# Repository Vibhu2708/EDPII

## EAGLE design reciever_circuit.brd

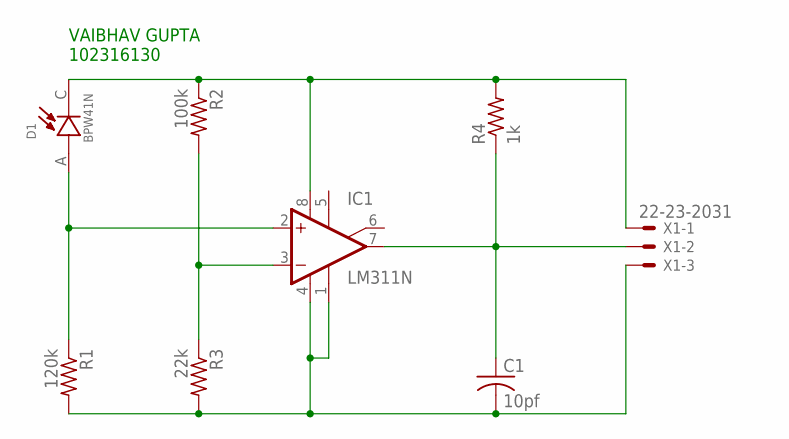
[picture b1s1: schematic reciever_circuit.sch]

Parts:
C1: 10pf; C025-024X044
D1: BPW41N; DIO_BPW41N
IC1: LM311N; DIL08
R1: 120k; 0204/5
R2: 100k; 0204/5
R3: 22k; 0204/5
R4: 1k; 0204/5
X1: 22-23-2031

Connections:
unnamed: D1.A, IC1.2 (+IN), R1.1
unnamed: IC1.3 (-IN), R2.2, R3.1
unnamed: D1.C, IC1.8 (V+), R2.1, R4.2, X1.1
unnamed: C1.1, IC1.7 (OUT), R4.1, X1.2
unnamed: C1.2, IC1.1 (GND), IC1.4 (V-), R1.2, R3.2, X1.3

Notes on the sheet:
VAIBHAV GUPTA 102316130

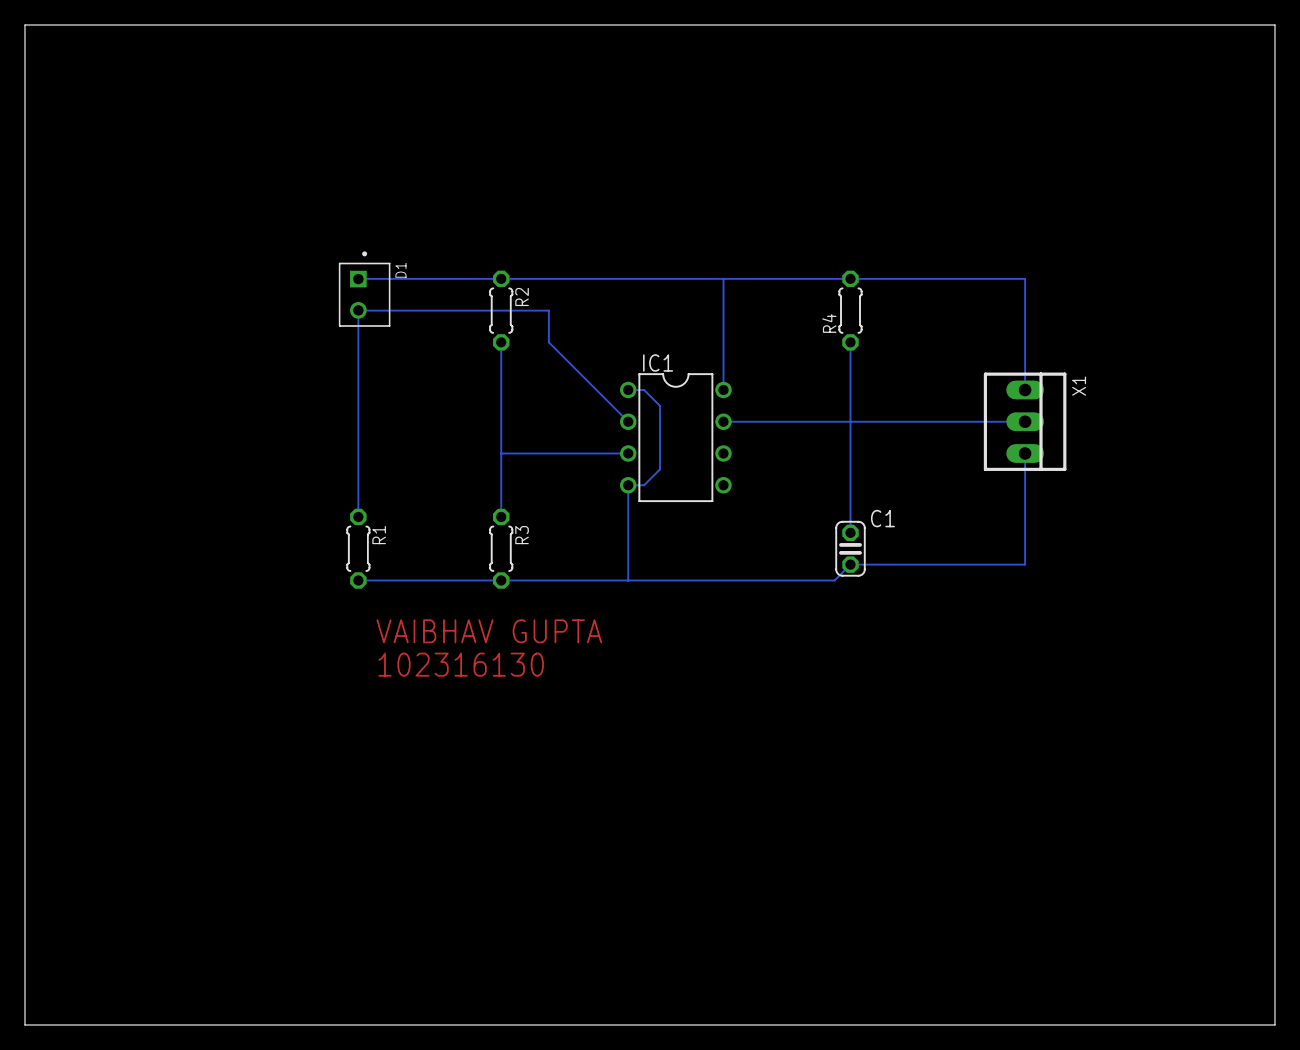
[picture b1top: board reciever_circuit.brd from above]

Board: 2 copper layers, 100.0 x 80.0 mm, 8 parts (0 on the bottom side), 5 nets.

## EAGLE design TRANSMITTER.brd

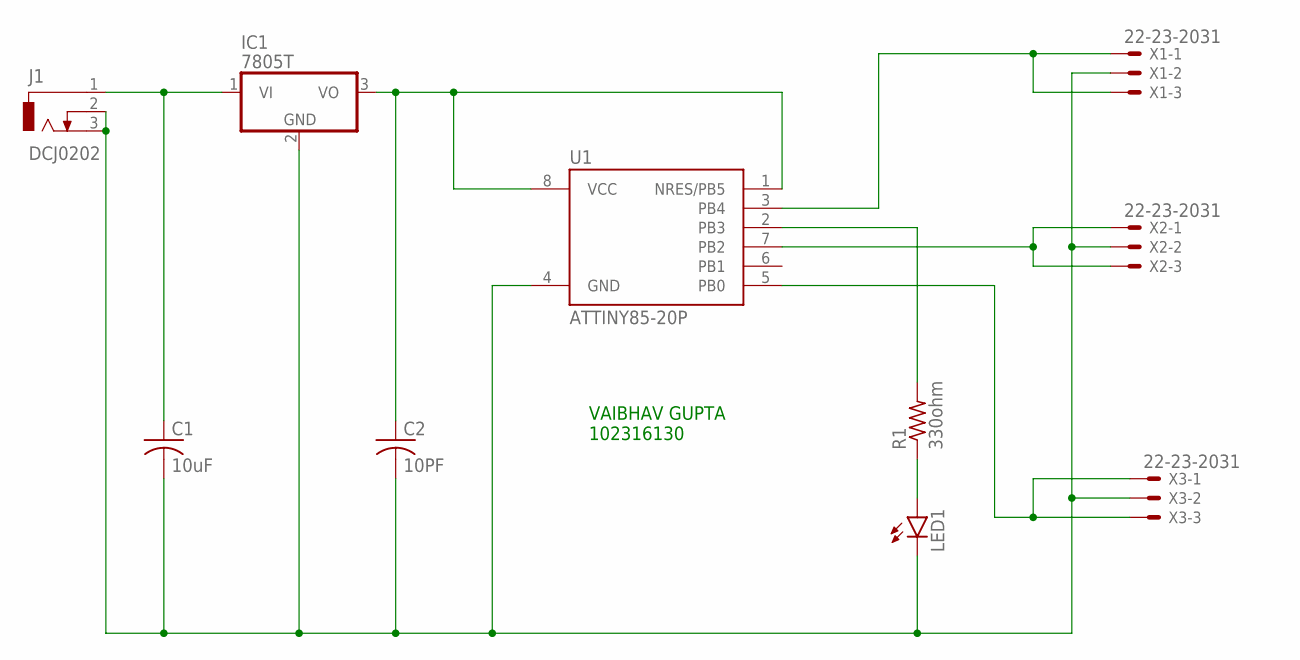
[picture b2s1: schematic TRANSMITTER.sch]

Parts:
C1: 10uF; C025-024X044
C2: 10PF; C025-024X044
IC1: 7805T; TO220H
J1: DCJ0202
LED1: LED3MM
R1: 330ohm; 0207/5V
U1: ATTINY85-20P; PDIP08_300MIL
X1, X2, X3: 22-23-2031

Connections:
unnamed: C1.1, IC1.1 (VI), J1.1
unnamed: C1.2, C2.2, IC1.2 (GND), J1.2, J1.3, LED1.K (C), U1.4 (GND), X1.2, X2.2, X3.2
unnamed: C2.1, IC1.3 (VO), U1.1 (NRES/PB5), U1.8 (VCC)
unnamed: U1.3 (PB4), X1.1, X1.3
unnamed: U1.5 (PB0), X3.1, X3.3
unnamed: R1.2, U1.2 (PB3)
unnamed: LED1.A, R1.1
unnamed: U1.7 (PB2), X2.1, X2.3

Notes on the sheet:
VAIBHAV GUPTA 102316130

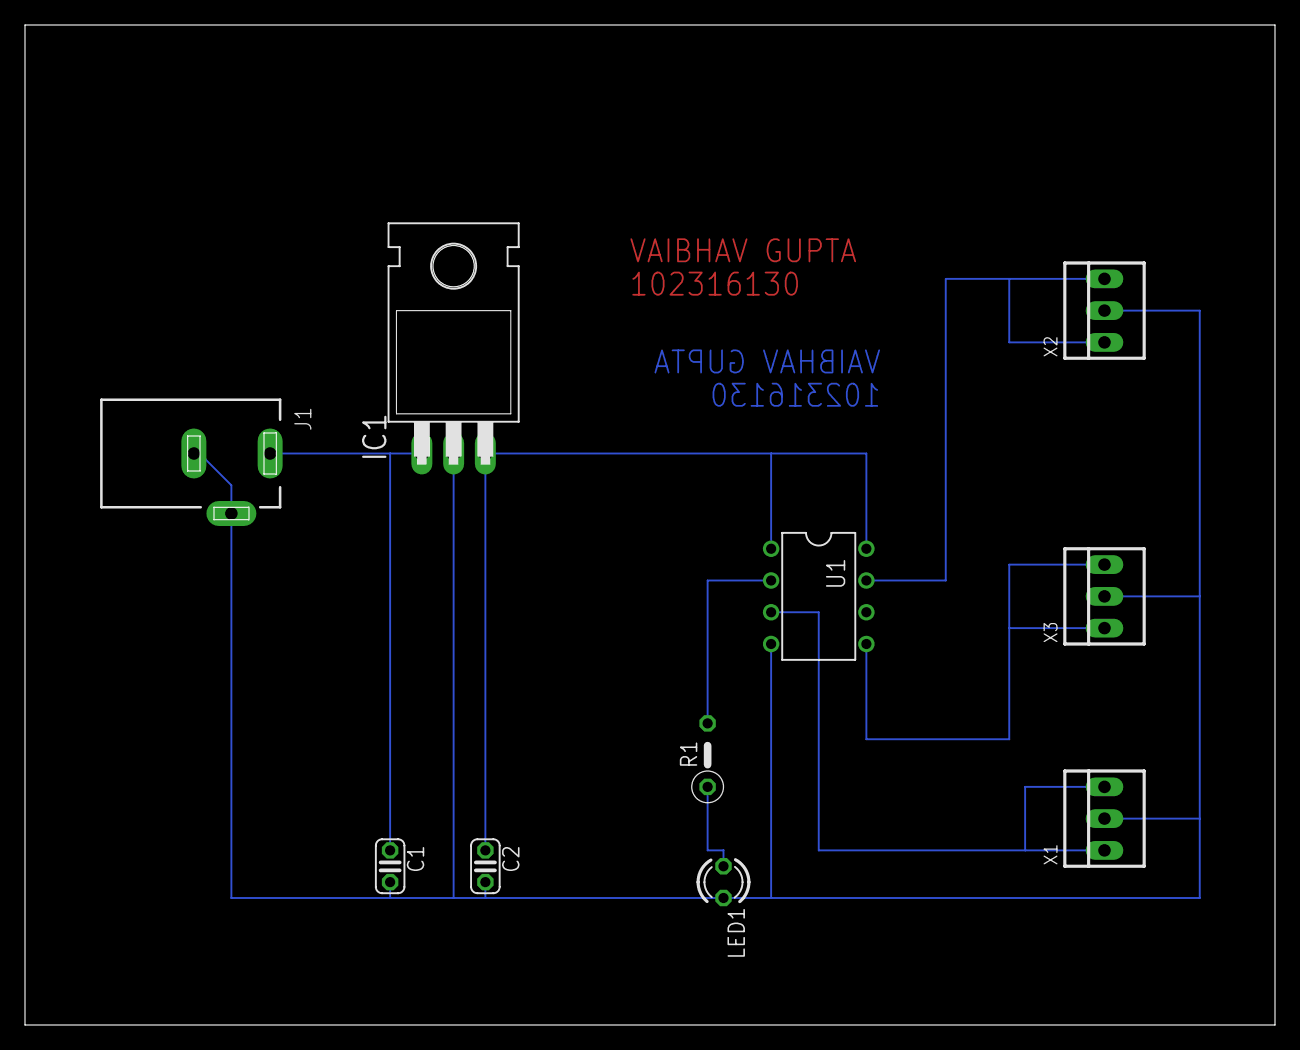
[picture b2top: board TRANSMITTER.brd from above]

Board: 2 copper layers, 100.0 x 80.0 mm, 10 parts (0 on the bottom side), 8 nets.

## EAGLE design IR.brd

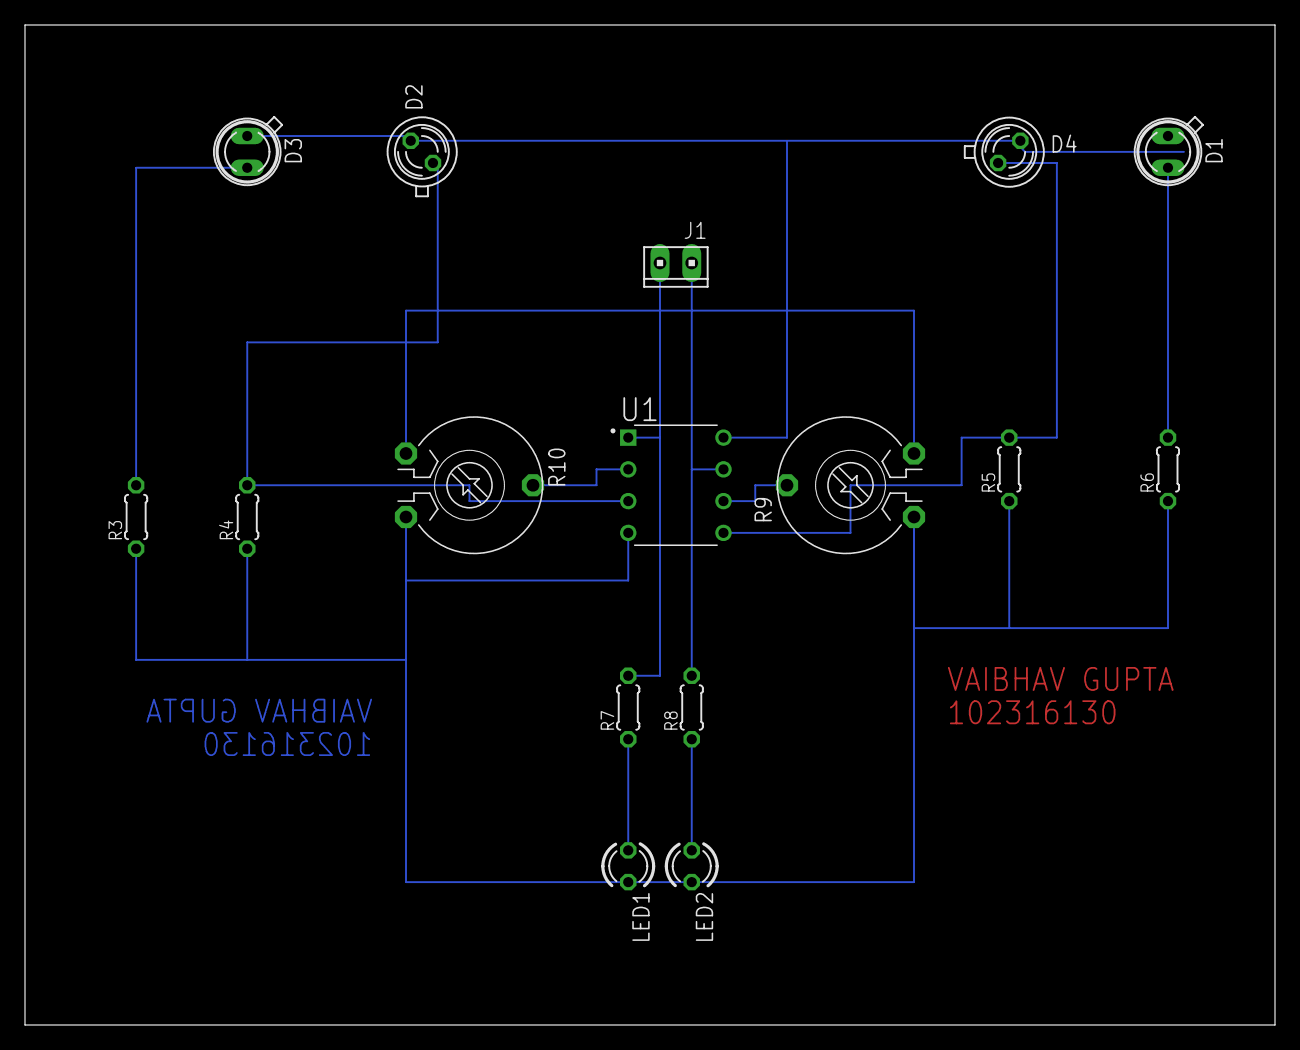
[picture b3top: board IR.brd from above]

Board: 2 copper layers, 100.0 x 80.0 mm, 16 parts (0 on the bottom side), 12 nets.

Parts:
D1, D3: SFH482
D2, D4: BPX65
J1: 10X02MTA
LED1, LED2: LED3MM
R3, R6, R7, R8: 330ohm; 0204/5
R4, R5: 10K; 0204/5
R9, R10: PT-10
U1: LM358N; DIP762W46P254L960H508Q8

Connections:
unnamed: J1.1, R7.2, U1.1
unnamed: LED1.A, R7.1
unnamed: LED2.A, R8.1
unnamed: J1.2, R8.2, U1.7
unnamed: R10.3, U1.2
unnamed: R9.3, U1.6
unnamed: LED1.K, LED2.K, R3.1, R4.1, R5.1, R6.1, R9.1, R10.2, U1.4
unnamed: D1.K, R6.2
unnamed: D4.A, R5.2, U1.5
unnamed: D1.A, D2.K, D3.A, D4.K, R9.2, R10.1, U1.8
unnamed: D3.K, R3.2
unnamed: D2.A, R4.2, U1.3
